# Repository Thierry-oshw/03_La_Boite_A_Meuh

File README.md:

# 03_La_Boite_A_Meuh
 La boite à Meuh!

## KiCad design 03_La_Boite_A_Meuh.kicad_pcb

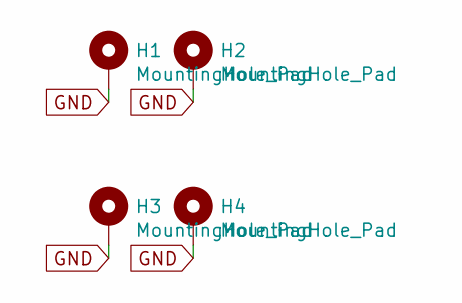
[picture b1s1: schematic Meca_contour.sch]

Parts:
H1, H2, H3, H4: MountingHole_Pad; MountingHole_3.2mm_M3_Pad_Via

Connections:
GND: H1.1, H2.1, H3.1, H4.1; also elsewhere on the board

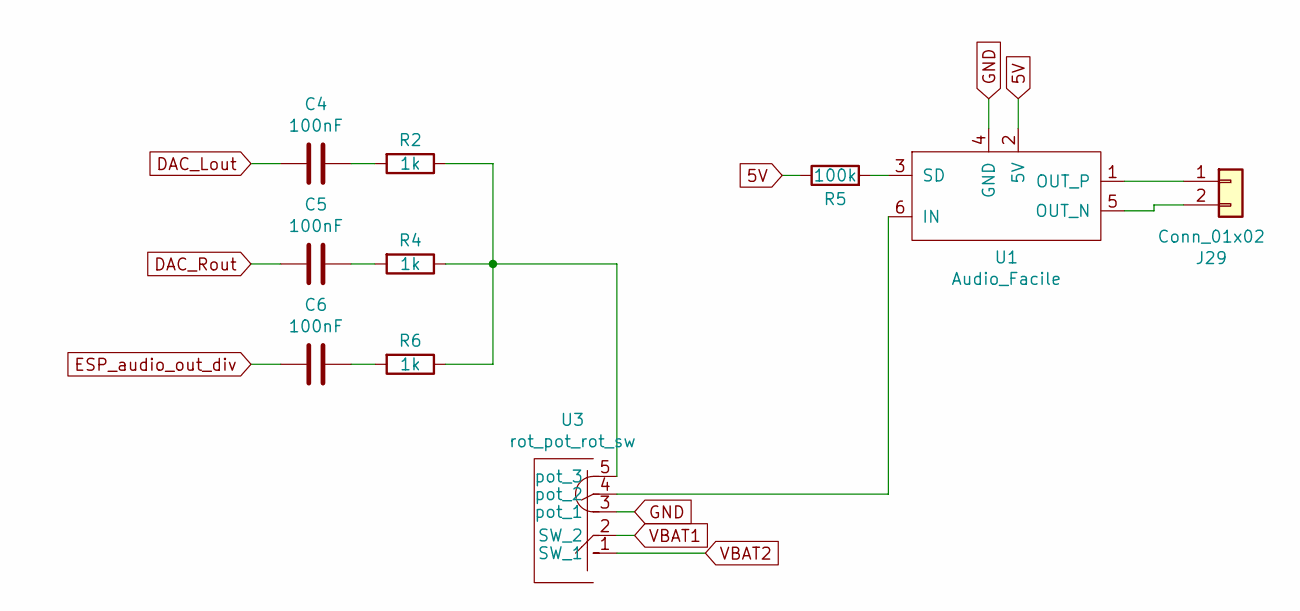
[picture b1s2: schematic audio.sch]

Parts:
C4, C5, C6: 100nF; C_0603_1608Metric_Pad1.05x0.95mm_HandSolder
J29: Conn_01x02; JST_XH_B2B-XH-A_1x02_P2.50mm_Vertical
R2, R4, R6: 1k; R_0603_1608Metric_Pad1.05x0.95mm_HandSolder
R5: 100k; R_0603_1608Metric_Pad1.05x0.95mm_HandSolder
U1: Audio_Facile; Audio_Facile_HP
U3: rot_pot_rot_sw; PTR901

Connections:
5V: R5.1, U1.2 (5V); also elsewhere on the board
DAC_Lout: C4.2; also elsewhere on the board
DAC_Rout: C5.2; also elsewhere on the board
ESP_audio_out_div: C6.2; also elsewhere on the board
GND: U1.4 (GND), U3.3 (pot_1); also elsewhere on the board
unnamed: C4.1, R2.2
unnamed: C5.1, R4.2
unnamed: C6.1, R6.2
unnamed: J29.1, U1.1 (OUT_P)
unnamed: J29.2, U1.5 (OUT_N)
unnamed: R2.1, R4.1, R6.1, U3.5 (pot_3)
unnamed: R5.2, U1.3 (SD)
unnamed: U1.6 (IN), U3.4 (pot_2)
VBAT1: U3.2 (SW_2); also elsewhere on the board
VBAT2: U3.1 (SW_1); also elsewhere on the board

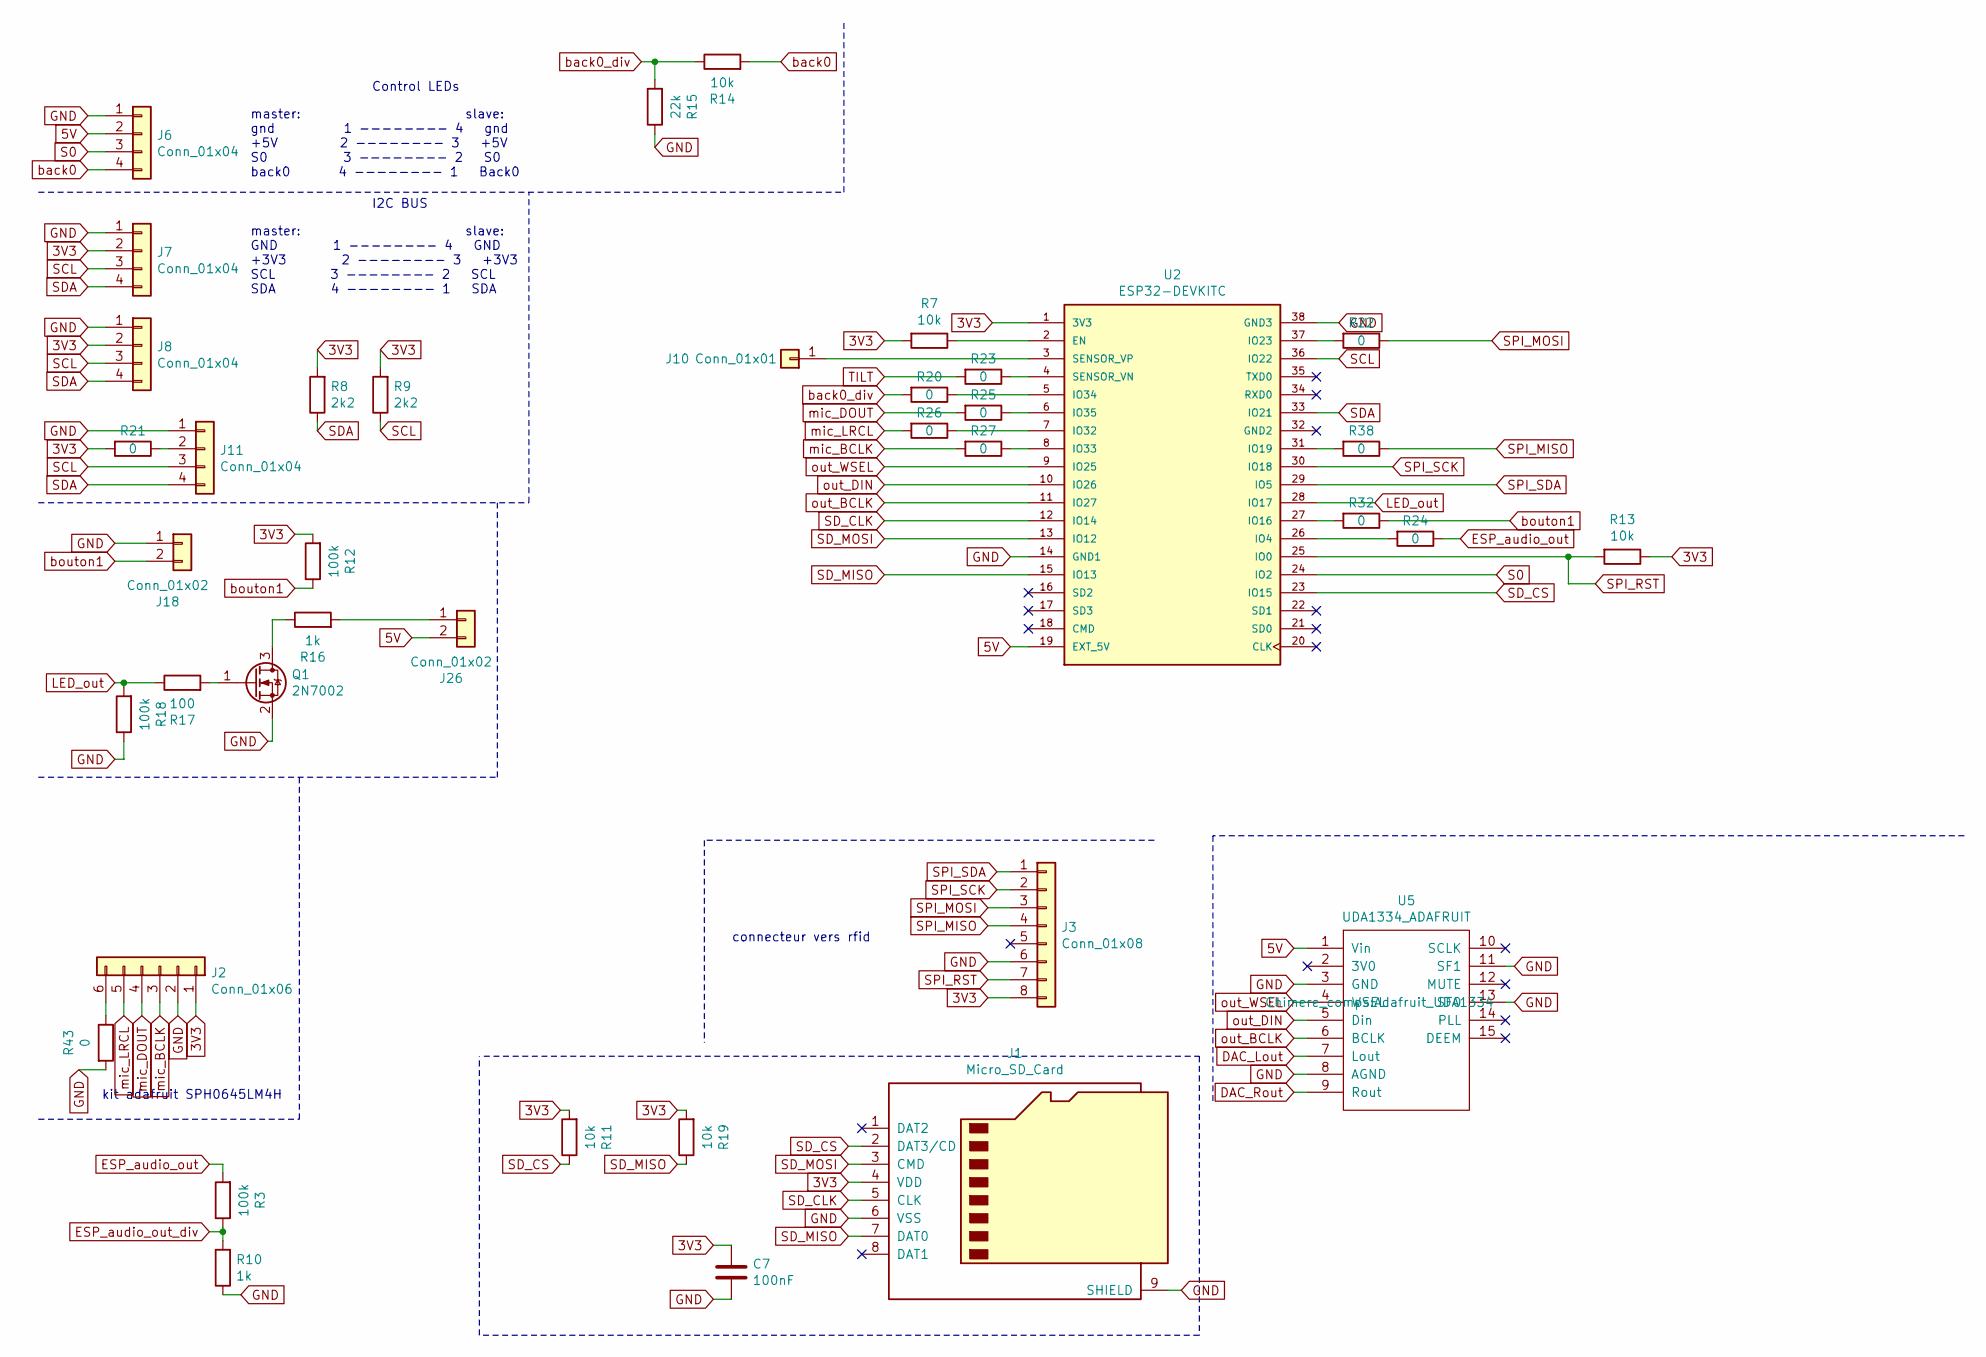
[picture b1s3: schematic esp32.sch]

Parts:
C7: 100nF; C_0603_1608Metric
J1: Micro_SD_Card; microSD_HC_Molex_104031-0811
J2: Conn_01x06; PinSocket_1x06_P2.54mm_Vertical
J3: Conn_01x08; PinSocket_1x08_P2.54mm_Vertical
J6: Conn_01x04; JST_XH_S4B-XH-A_1x04_P2.50mm_Horizontal
J7, J8, J11: Conn_01x04; JST_XH_B4B-XH-A_1x04_P2.50mm_Vertical
J10: Conn_01x01; PinHeader_1x01_P2.54mm_Vertical
J18, J26: Conn_01x02; JST_XH_B2B-XH-A_1x02_P2.50mm_Vertical
Q1: 2N7002; SOT-23
R3, R12, R18: 100k; R_0603_1608Metric_Pad1.05x0.95mm_HandSolder
R7, R11, R13, R14, R19: 10k; R_0603_1608Metric_Pad1.05x0.95mm_HandSolder
R8, R9: 2k2; R_0603_1608Metric_Pad1.05x0.95mm_HandSolder
R10, R16: 1k; R_0603_1608Metric_Pad1.05x0.95mm_HandSolder
R15: 22k; R_0603_1608Metric_Pad1.05x0.95mm_HandSolder
R17: 100; R_0603_1608Metric_Pad1.05x0.95mm_HandSolder
R20, R21, R22, R23, R24, R25, R26, R27, R32, R38, R43: 0; R_0603_1608Metric_Pad1.05x0.95mm_HandSolder
U2: ESP32-DEVKITC; MODULE_ESP32-DEVKITC; PARTREV N/A
U5: UDA1334_ADAFRUIT; Adafruit_UDA1334

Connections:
3V3: C7.1, J1.4 (VDD), J2.1, J3.8, J7.2, J8.2, R7.2, R8.2, R9.2, R11.2, R12.2, R13.1, R19.2, R21.2, U2.1 (3V3); also elsewhere on the board
5V: J6.2, J26.2, U2.19 (EXT_5V), U5.1 (Vin); also elsewhere on the board
DAC_Lout: U5.7 (Lout); also elsewhere on the board
DAC_Rout: U5.9 (Rout); also elsewhere on the board
ESP_audio_out: R3.2, R24.1
ESP_audio_out_div: R3.1, R10.2; also elsewhere on the board
GND: C7.2, J1.6 (VSS), J1.9 (SHIELD), J2.2, J3.6, J6.1, J7.1, J8.1, J11.1, J18.1, Q1.2 (S), R10.1, R15.1, R18.1, R43.2, U2.14 (GND1), U2.38 (GND3), U5.3 (GND), U5.8 (AGND), U5.11 (SF1), U5.13 (SF0); also elsewhere on the board
LED_out: R17.1, R18.2, U2.28 (IO17)
unnamed: J2.6, R43.1
unnamed: J10.1, U2.3 (SENSOR_VP)
unnamed: J11.2, R21.1
unnamed: J26.1, R16.2
unnamed: Q1.1 (G), R17.2
unnamed: Q1.3 (D), R16.1
unnamed: R7.1, U2.2 (EN)
unnamed: R20.1, U2.5 (IO34)
unnamed: R22.2, U2.37 (IO23)
unnamed: R23.1, U2.4 (SENSOR_VN)
unnamed: R24.2, U2.26 (IO4)
unnamed: R25.1, U2.6 (IO35)
unnamed: R26.1, U2.7 (IO32)
unnamed: R27.1, U2.8 (IO33)
unnamed: R32.2, U2.27 (IO16)
unnamed: R38.2, U2.31 (IO19)
S0: J6.3, U2.24 (IO2)
SCL: J7.3, J8.3, J11.3, R9.1, U2.36 (IO22)
SDA: J7.4, J8.4, J11.4, R8.1, U2.33 (IO21)
SD_CLK: J1.5 (CLK), U2.12 (IO14)
SD_CS: J1.2 (DAT3/CD), R11.1, U2.23 (IO15)
SD_MISO: J1.7 (DAT0), R19.1, U2.15 (IO13)
SD_MOSI: J1.3 (CMD), U2.13 (IO12)
SPI_MISO: J3.4, R38.1
SPI_MOSI: J3.3, R22.1
SPI_RST: J3.7, R13.2, U2.25 (IO0)
SPI_SCK: J3.2, U2.30 (IO18)
SPI_SDA: J3.1, U2.29 (IO5)
TILT: R23.2; also elsewhere on the board
back0: J6.4, R14.2
back0_div: R14.1, R15.2, R20.2
bouton1: J18.2, R12.1, R32.1
mic_BCLK: J2.3, R27.2
mic_DOUT: J2.4, R25.2
mic_LRCL: J2.5, R26.2
out_BCLK: U2.11 (IO27), U5.6 (BCLK)
out_DIN: U2.10 (IO26), U5.5 (Din)
out_WSEL: U2.9 (IO25), U5.4 (WSEL)

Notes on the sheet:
Control LEDs
master: slave: gnd 1 -------- 4 gnd +5V 2 -------- 3 +5V S0 3 -------- 2 S0 back0 4 -------- 1 Back0
I2C BUS
master: slave: GND 1 -------- 4 GND +3V3 2 -------- 3 +3V3 SCL 3 -------- 2 SCL SDA 4 -------- 1 SDA
kit adafruit SPH0645LM4H
connecteur vers rfid

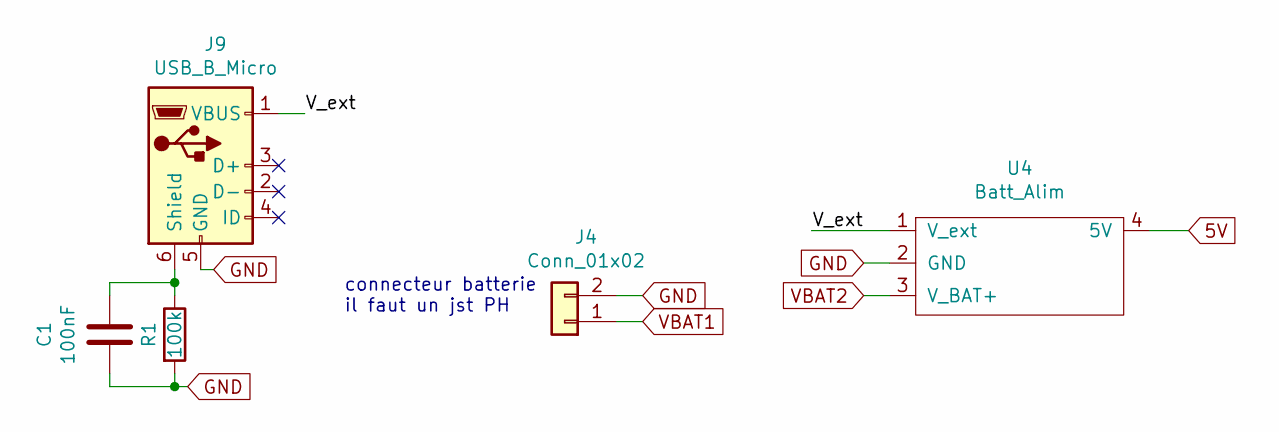
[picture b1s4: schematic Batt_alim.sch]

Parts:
C1: 100nF; C_0603_1608Metric_Pad1.05x0.95mm_HandSolder
J4: Conn_01x02; JST_PH_B2B-PH-K_1x02_P2.00mm_Vertical
J9: USB_B_Micro; USB_Micro-B_Wuerth_629105150521_CircularHoles
R1: 100k; R_0603_1608Metric_Pad1.05x0.95mm_HandSolder
U4: Batt_Alim; Batt_Alim_4P_HP

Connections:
5V: U4.4 (5V); also elsewhere on the board
/Batt_alim/V_ext: J9.1 (VBUS), U4.1 (V_ext)
GND: C1.2, J4.2, J9.5 (GND), R1.2, U4.2 (GND); also elsewhere on the board
unnamed: C1.1, J9.6 (Shield), R1.1
VBAT1: J4.1; also elsewhere on the board
VBAT2: U4.3 (V_BAT+); also elsewhere on the board

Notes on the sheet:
connecteur batterie il faut un jst PH

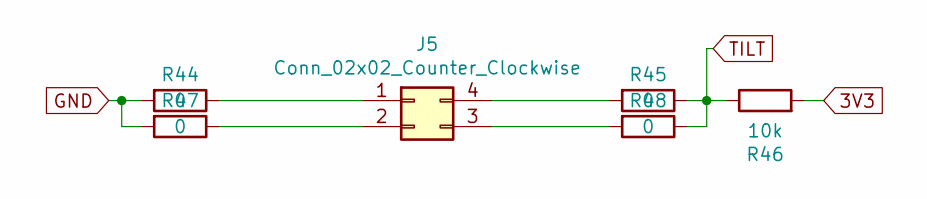
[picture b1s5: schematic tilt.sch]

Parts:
J5: Conn_02x02_Counter_Clockwise; PinSocket_2x02_P2.54mm_Vertical
R44, R45, R47, R48: 0; R_0603_1608Metric_Pad1.05x0.95mm_HandSolder
R46: 10k; R_0603_1608Metric_Pad1.05x0.95mm_HandSolder

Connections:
3V3: R46.2; also elsewhere on the board
GND: R44.2, R47.2; also elsewhere on the board
unnamed: J5.1, R44.1
unnamed: J5.2, R47.1
unnamed: J5.3, R48.2
unnamed: J5.4, R45.2
TILT: R45.1, R46.1, R48.1; also elsewhere on the board

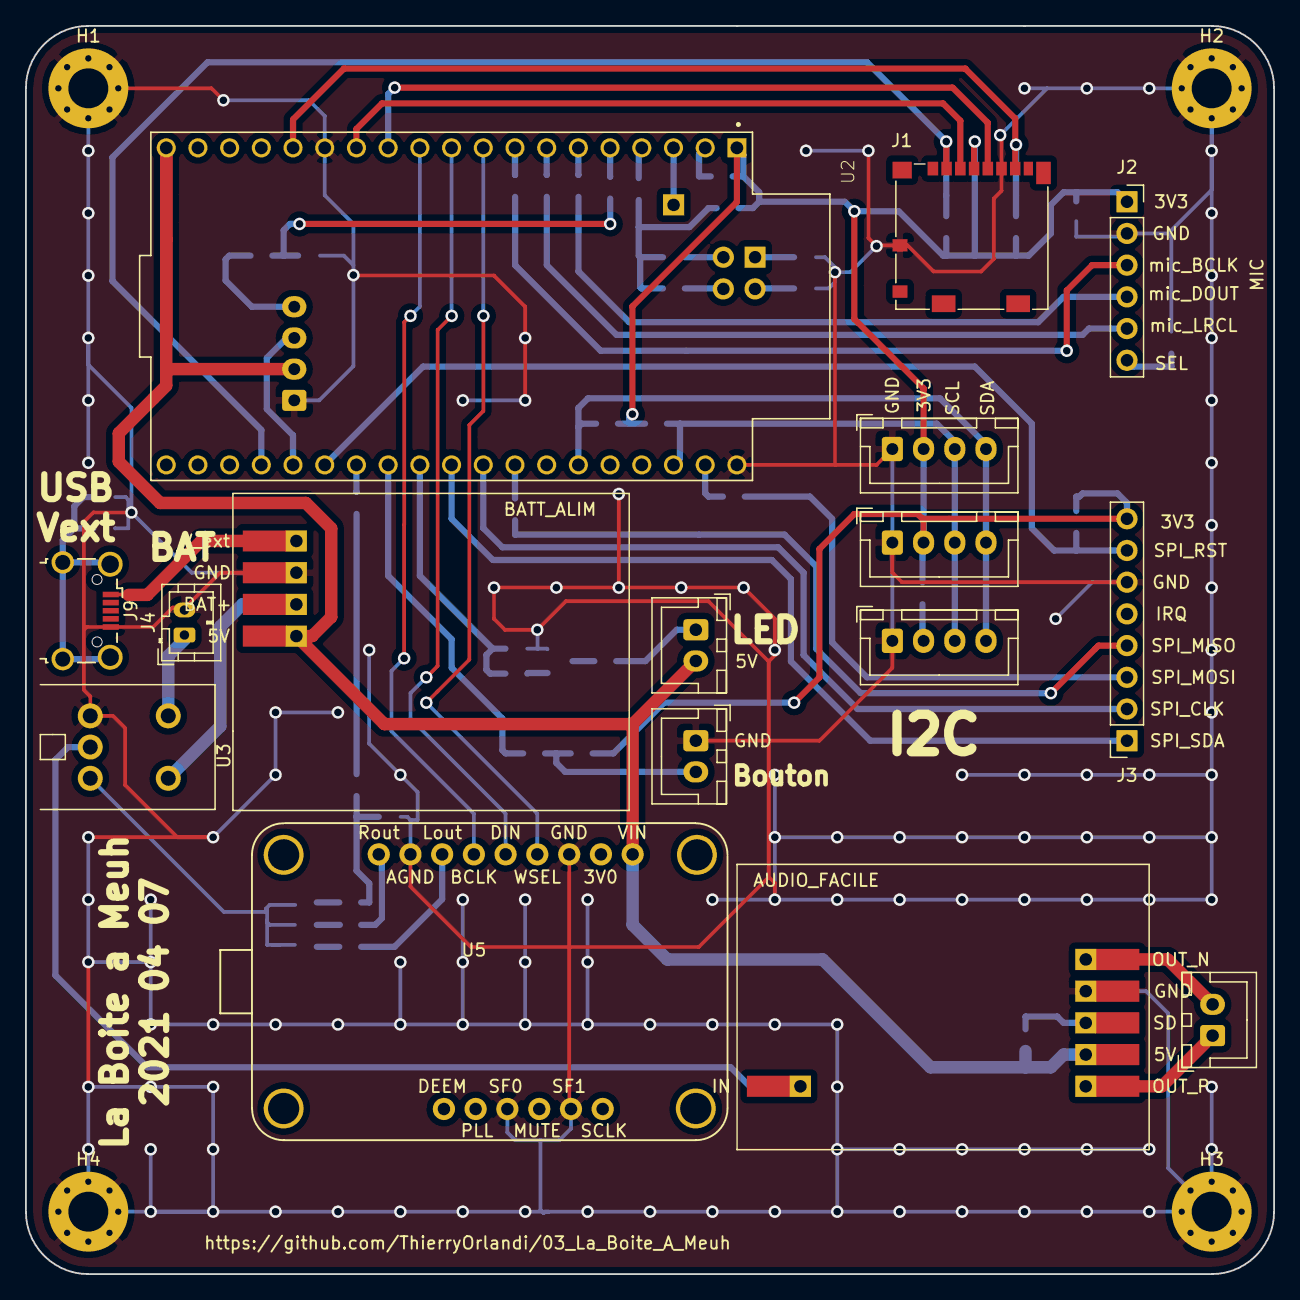
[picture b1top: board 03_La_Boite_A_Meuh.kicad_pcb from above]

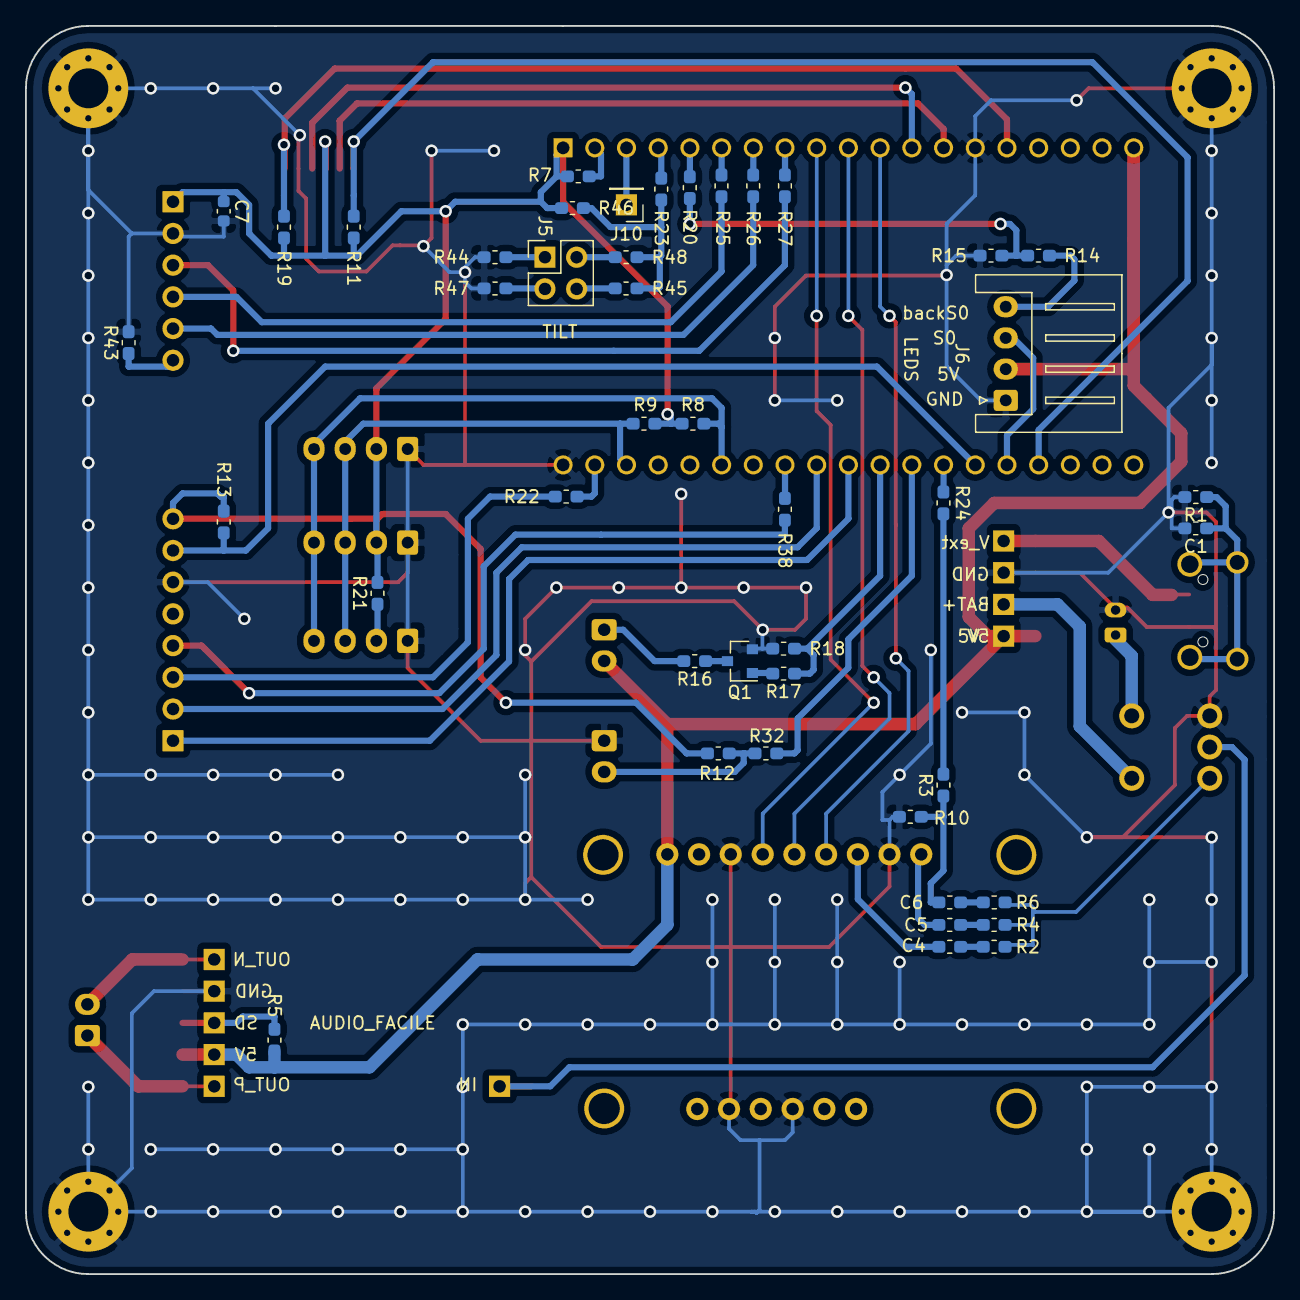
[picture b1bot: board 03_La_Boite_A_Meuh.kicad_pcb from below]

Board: 2 copper layers, 100.0 x 100.0 mm, 64 parts (44 on the bottom side), 62 nets.

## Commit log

2020-11-30 Delete fp-info-cache
    no need for this huge file
2020-12-01 deleted files
    removed unnecessary unziped files
2020-12-01 add esp32 && mp3 player
2020-12-01 end of day save
2020-12-03 ajout de la licence; added license.
2020-12-06 gitignore set to kicad version
2020-12-20 useless files to keep removed from index
2020-12-20 batt_alim module added
2020-12-20 added battery footprint
    and some net names
2020-12-20 removed from index useless files
2020-12-22 fin schéma, début placement
2020-12-23 placement ok
2020-12-23 routing + generation gerber
2021-01-16 ajout site web intéressant.
2021-01-30 added picture
2021-02-13 simplifying + proper pins for uart + sd card host implemented
2021-03-07 maj
    simplification dfr
2021-03-24 inversion miso et mosi sdcard
    problème de pull-up au démarrage qui bloque l'esp32. Résolu en permutant les deux fils. schéma et routage corrigés
2021-04-05 simplification
    effacé les straps des fonctions sd card et dac audio
2021-04-05 changement connecteur
    utilisation d'un connecteur usb micro pour l'alimentation
2021-04-06 modification audio + alim
    utilisation du module Audio_Facile
    + utilisation d'un rotary switch rotary potentiometer
2021-04-06 UDA1334
    utilisation symbole et empreinte compléte du module adafruit uda1334 à la place du simple connecteur
2021-04-06 ajout spi + placement + routage
2021-04-07 correction pcb
    ajout infos sur silk
    changement connecteur jst xh 4 points pour un coudé.
2021-04-09 ajout strap sur dernier connecteur I2C
2021-04-19 maj de kicad: problème bibliothèque
2021-05-26 chgt connecteur batterie
    connecteur batterie JST XH changé pour un PH + inversion des fils. schéma + routage fait
2021-07-22 maj libraire composants
2021-07-24 maj split librairie
2021-09-14 passage à la version "HP" de audio facile
2021-09-14 Changement pour Batt_alim_4P version _HP
2023-05-02 chgt nom fichier licence
